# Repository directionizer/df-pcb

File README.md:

# df-pcb

Directionizer is a student project by Mason Ahner, Jared Beller, and John Fiorini for the spring 2021 session of ECE 2804 at Virginia Tech. The "directionizer" is a handheld device for locating a 1 kHz audio beacon. This repository contains KiCad schematics and PCBs for the directionizer hardware.

## Structure

The original design made during prototyping can be found in [schematic](schematic/). This was broken into three individual boards, which are stacked to form the final device. From bottom to top, the boards are [processing](processing/), [audio](audio/), and [display](display/). Each board's schematic and layout is in it's respective folder. For manufacturing, the three boards were combined into a panel. The final panel layout can be seen in the [panel](panel/) folder. Files sent to the board house, including gerbers, a bom, and smt placement, are in the [production](production/) folder.

## Licensing

Copyright (C) 2021  Mason Ahner, Jared Beller, and John Fiorini

This program is released under the [GNU General Public License, Version 3](https://www.gnu.org/licenses/gpl-3.0.txt) or later. See [LICENSE](LICENSE) for more information.

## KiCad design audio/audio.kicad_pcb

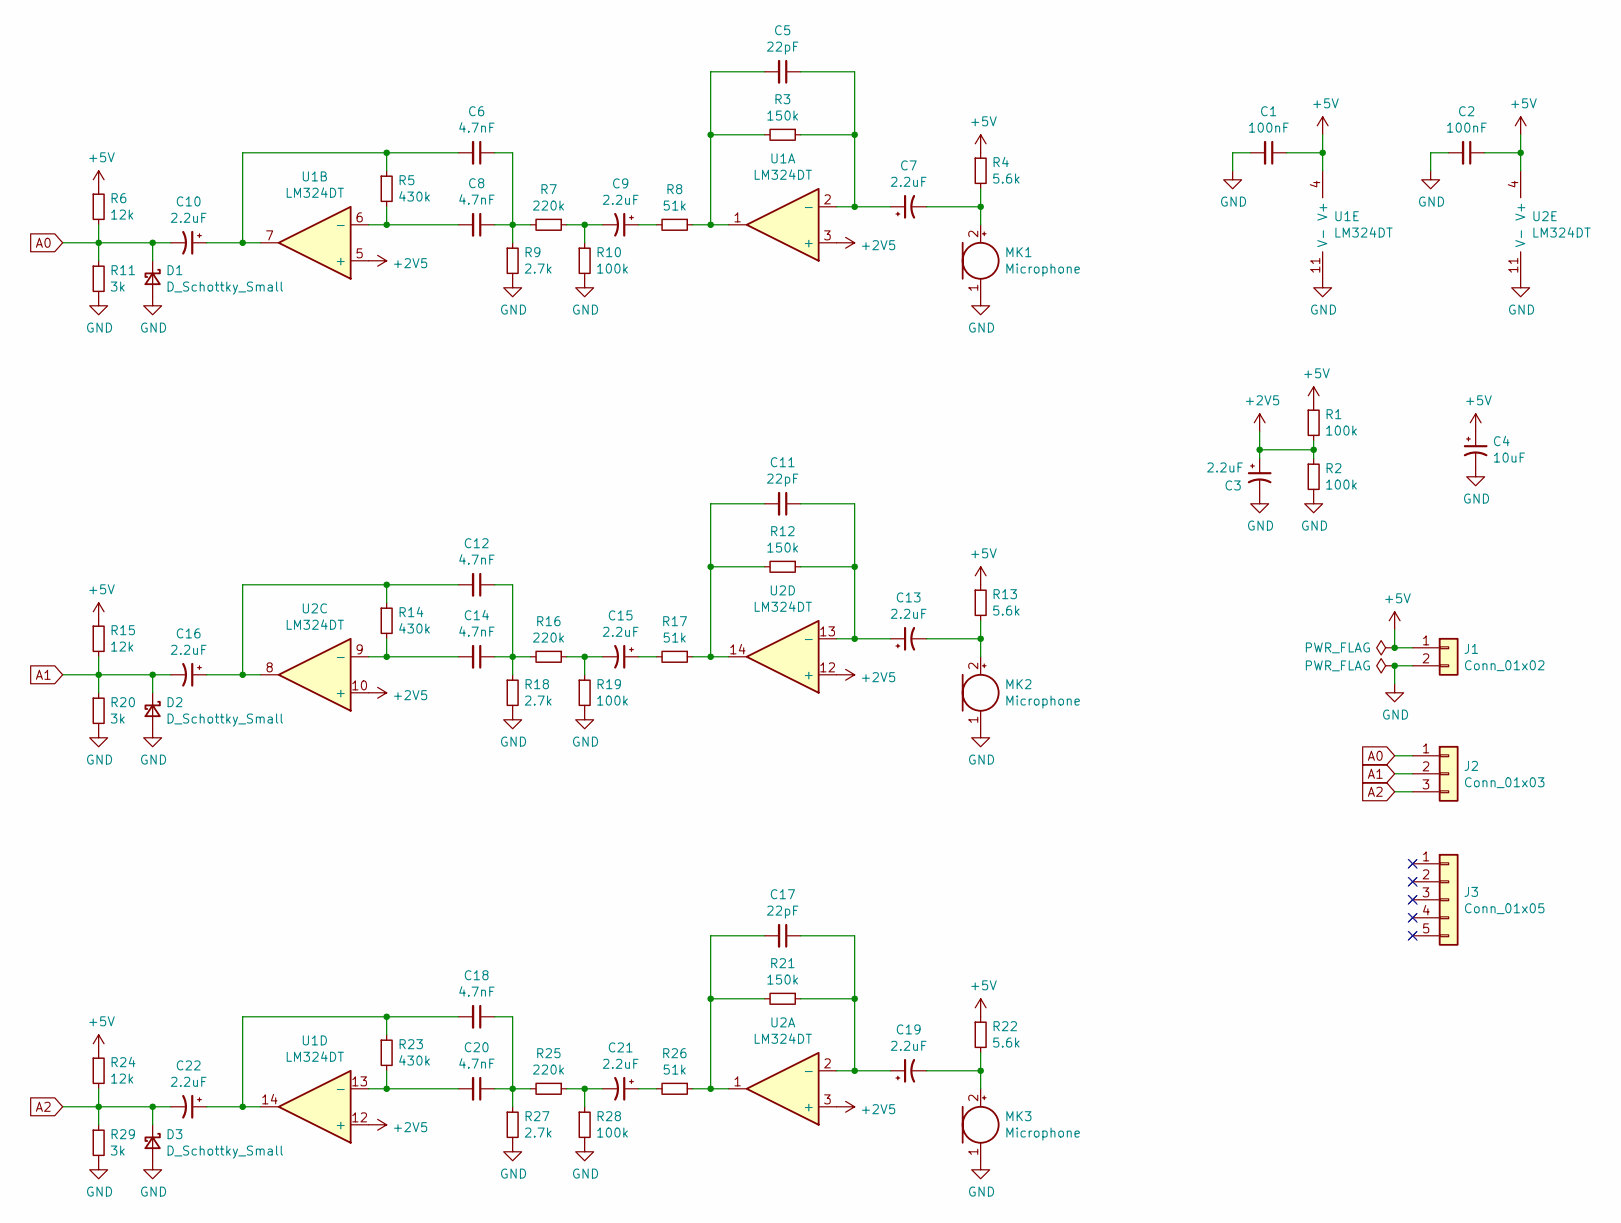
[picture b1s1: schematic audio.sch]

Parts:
C1, C2: 100nF; C_0603_1608Metric
C3, C7, C9, C10, C13, C15, C16, C19, C21, C22: 2.2uF; CP_EIA-3216-18_Kemet-A
C4: 10uF; CP_EIA-3216-18_Kemet-A
C5, C11, C17: 22pF; C_0603_1608Metric
C6, C8, C12, C14, C18, C20: 4.7nF; C_0603_1608Metric
D1, D2, D3: D_Schottky_Small; D_SOD-123
J1: Conn_01x02; 310-XX-102-41-001000
J2: Conn_01x03; 310-XX-103-41-001000
J3: Conn_01x05; 310-XX-105-41-001000
MK1, MK2, MK3: Microphone; CMA-6542PF
R1, R2, R10, R19, R28: 100k; R_0603_1608Metric
R3, R12, R21: 150k; R_0603_1608Metric
R4, R13, R22: 5.6k; R_0603_1608Metric
R5, R14, R23: 430k; R_0603_1608Metric
R6, R15, R24: 12k; R_0603_1608Metric
R7, R16, R25: 220k; R_0603_1608Metric
R8, R17, R26: 51k; R_0603_1608Metric
R9, R18, R27: 2.7k; R_0603_1608Metric
R11, R20, R29: 3k; R_0603_1608Metric
U1, U2: LM324DT; SOIC-14_3.9x8.7mm_P1.27mm

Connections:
+2V5: C3.1, R1.2, R2.1, U1.3 (+), U1.5 (+), U1.12 (+), U2.3 (+), U2.10 (+), U2.12 (+)
+5V: C1.1, C2.1, C4.1, J1.1, R1.1, R4.1, R6.1, R13.1, R15.1, R22.1, R24.1, U1.4 (V+), U2.4 (V+)
A0: C10.2, D1.1 (K), J2.1, R6.2, R11.1
A1: C16.2, D2.1 (K), J2.2, R15.2, R20.1
A2: C22.2, D3.1 (K), J2.3, R24.2, R29.1
GND: C1.2, C2.2, C3.2, C4.2, D1.2 (A), D2.2 (A), D3.2 (A), J1.2, MK1.1 (-), MK2.1 (-), MK3.1 (-), R2.2, R9.2, R10.2, R11.2, R18.2, R19.2, R20.2, R27.2, R28.2, R29.2, U1.11 (V-), U2.11 (V-)
unnamed: C5.1, C7.1, R3.1, U1.2 (-)
unnamed: C5.2, R3.2, R8.1, U1.1
unnamed: C6.1, C8.1, R7.2, R9.1
unnamed: C7.2, MK1.2 (+), R4.2
unnamed: C8.2, R5.2, U1.6 (-)
unnamed: C9.1, R8.2
unnamed: C9.2, R7.1, R10.1
unnamed: C6.2, C10.1, R5.1, U1.7
unnamed: C11.1, C13.1, R12.1, U2.13 (-)
unnamed: C11.2, R12.2, R17.1, U2.14
unnamed: C12.1, C14.1, R16.2, R18.1
unnamed: C12.2, C16.1, R14.1, U2.8
unnamed: C13.2, MK2.2 (+), R13.2
unnamed: C14.2, R14.2, U2.9 (-)
unnamed: C15.1, R17.2
unnamed: C15.2, R16.1, R19.1
unnamed: C17.1, C19.1, R21.1, U2.2 (-)
unnamed: C17.2, R21.2, R26.1, U2.1
unnamed: C18.1, C20.1, R25.2, R27.1
unnamed: C18.2, C22.1, R23.1, U1.14
unnamed: C19.2, MK3.2 (+), R22.2
unnamed: C20.2, R23.2, U1.13 (-)
unnamed: C21.1, R26.2
unnamed: C21.2, R25.1, R28.1

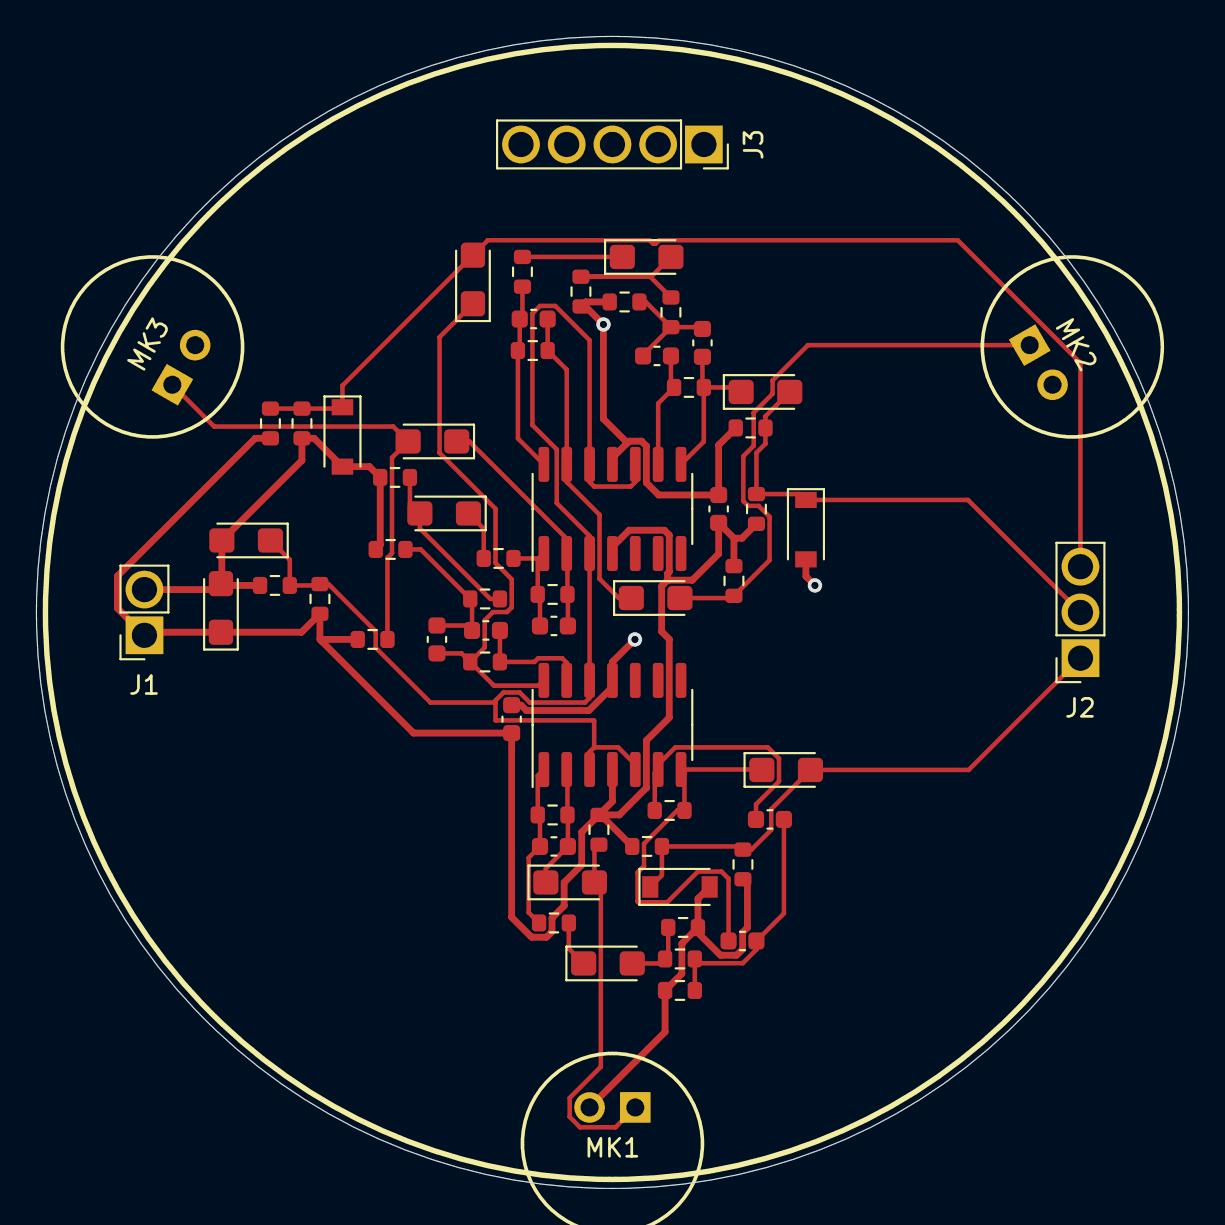
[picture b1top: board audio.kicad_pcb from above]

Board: 2 copper layers, 64.0 x 64.0 mm, 62 parts (0 on the bottom side), 30 nets.

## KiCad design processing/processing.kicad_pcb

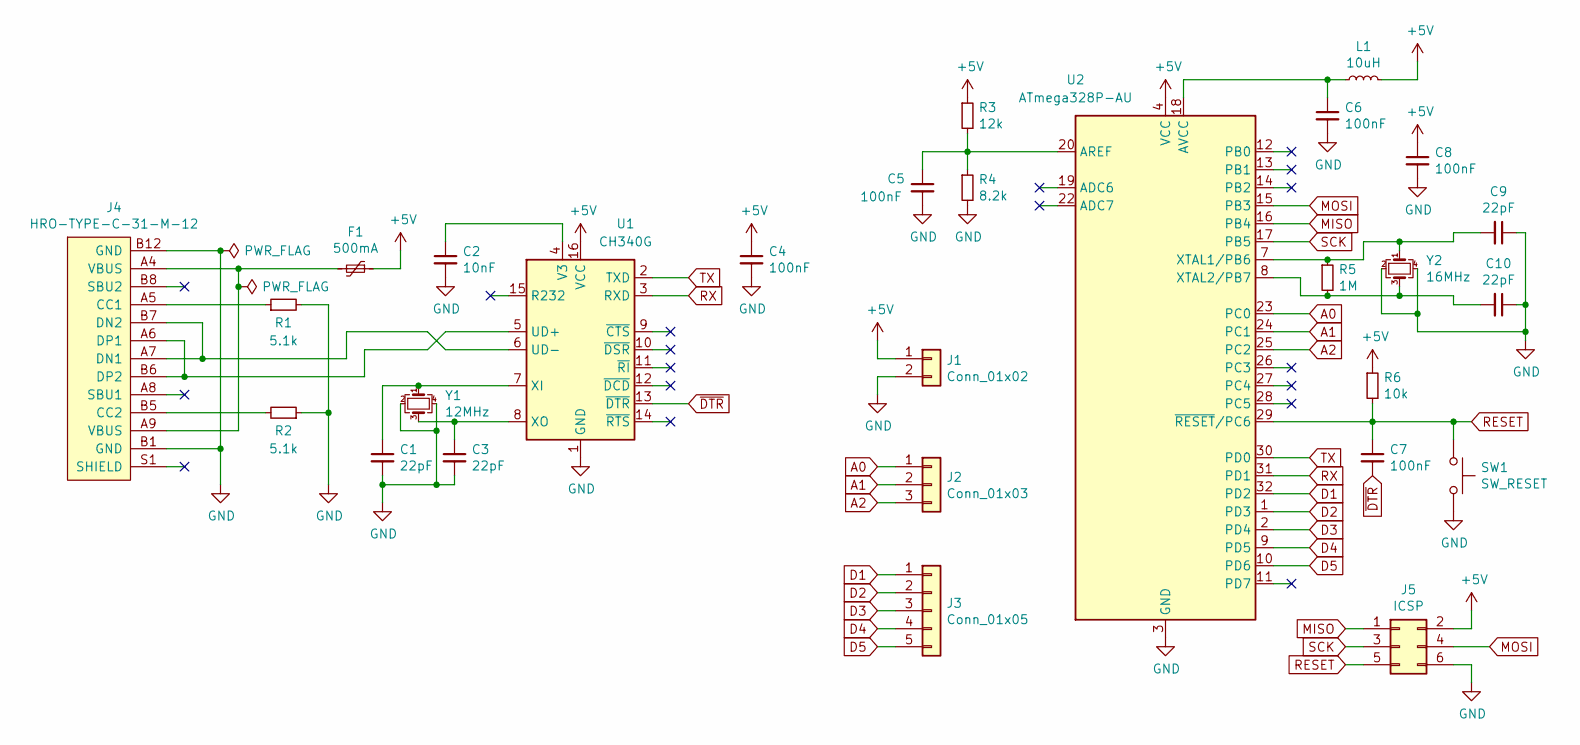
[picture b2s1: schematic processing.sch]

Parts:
C1, C3, C9, C10: 22pF; C_0603_1608Metric
C2: 10nF; C_0603_1608Metric
C4, C5, C6, C7, C8: 100nF; C_0603_1608Metric
F1: 500mA; Fuse_1206_3216Metric_Pad1.42x1.75mm_HandSolder
J1: Conn_01x02; 310-XX-102-41-001000
J2: Conn_01x03; 310-XX-103-41-001000
J3: Conn_01x05; 310-XX-105-41-001000
J4: HRO-TYPE-C-31-M-12; USB_C_Receptacle_HRO_TYPE-C-31-M-12
J5: ICSP; PinHeader_2x03_P2.54mm_Vertical
L1: 10uH; L_0805_2012Metric
R1, R2: 5.1k; R_0603_1608Metric
R3: 12k; R_0603_1608Metric
R4: 8.2k; R_0603_1608Metric
R5: 1M; R_0603_1608Metric
R6: 10k; R_1206_3216Metric
SW1: SW_RESET; SW_SPST_SKQG_WithoutStem
U1: CH340G; SOIC-16_3.9x9.9mm_P1.27mm
U2: ATmega328P-AU; TQFP-32_7x7mm_P0.8mm
Y1: 12MHz; Crystal_SMD_3225-4Pin_3.2x2.5mm
Y2: 16MHz; Crystal_SMD_3225-4Pin_3.2x2.5mm

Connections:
+5V: C4.1, C8.1, F1.1, J1.1, J5.2, L1.2, R3.1, R6.1, U1.16 (VCC), U2.4 (VCC), U2.6 (VCC)
A0: J2.1, U2.23 (PC0)
A1: J2.2, U2.24 (PC1)
A2: J2.3, U2.25 (PC2)
D1: J3.1, U2.32 (PD2)
D2: J3.2, U2.1 (PD3)
D3: J3.3, U2.2 (PD4)
D4: J3.4, U2.9 (PD5)
D5: J3.5, U2.10 (PD6)
GND: C1.2, C2.2, C3.2, C4.2, C5.2, C6.2, C8.2, C9.1, C10.1, J1.2, J4.B1 (GND), J4.B12 (GND), J5.6, R1.2, R2.1, R4.2, SW1.2, U1.1 (GND), U2.3 (GND), U2.5 (GND), U2.21 (GND), Y1.2, Y1.4, Y2.2, Y2.4
MISO: J5.1, U2.16 (PB4)
MOSI: J5.4, U2.15 (PB3)
unnamed: C1.1, U1.7 (XI), Y1.1
unnamed: C2.1, U1.4 (V3)
unnamed: C3.1, U1.8 (XO), Y1.3
unnamed: C5.1, R3.2, R4.1, U2.20 (AREF)
unnamed: C6.1, L1.1, U2.18 (AVCC)
unnamed: C9.2, R5.1, U2.7 (XTAL1/PB6), Y2.1
unnamed: C10.2, R5.2, U2.8 (XTAL2/PB7), Y2.3
unnamed: F1.2, J4.A4 (VBUS), J4.A9 (VBUS)
unnamed: J4.A5 (CC1), R1.1
unnamed: J4.A6 (DP1), J4.B6 (DP2), U1.5 (UD+)
unnamed: J4.A7 (DN1), J4.B7 (DN2), U1.6 (UD-)
unnamed: J4.B5 (CC2), R2.2
RESET: C7.1, J5.5, R6.2, SW1.1, U2.29 (~RESET~/PC6)
RX: U1.3 (RXD), U2.31 (PD1)
SCK: J5.3, U2.17 (PB5)
TX: U1.2 (TXD), U2.30 (PD0)
~DTR: C7.2, U1.13 (~DTR)

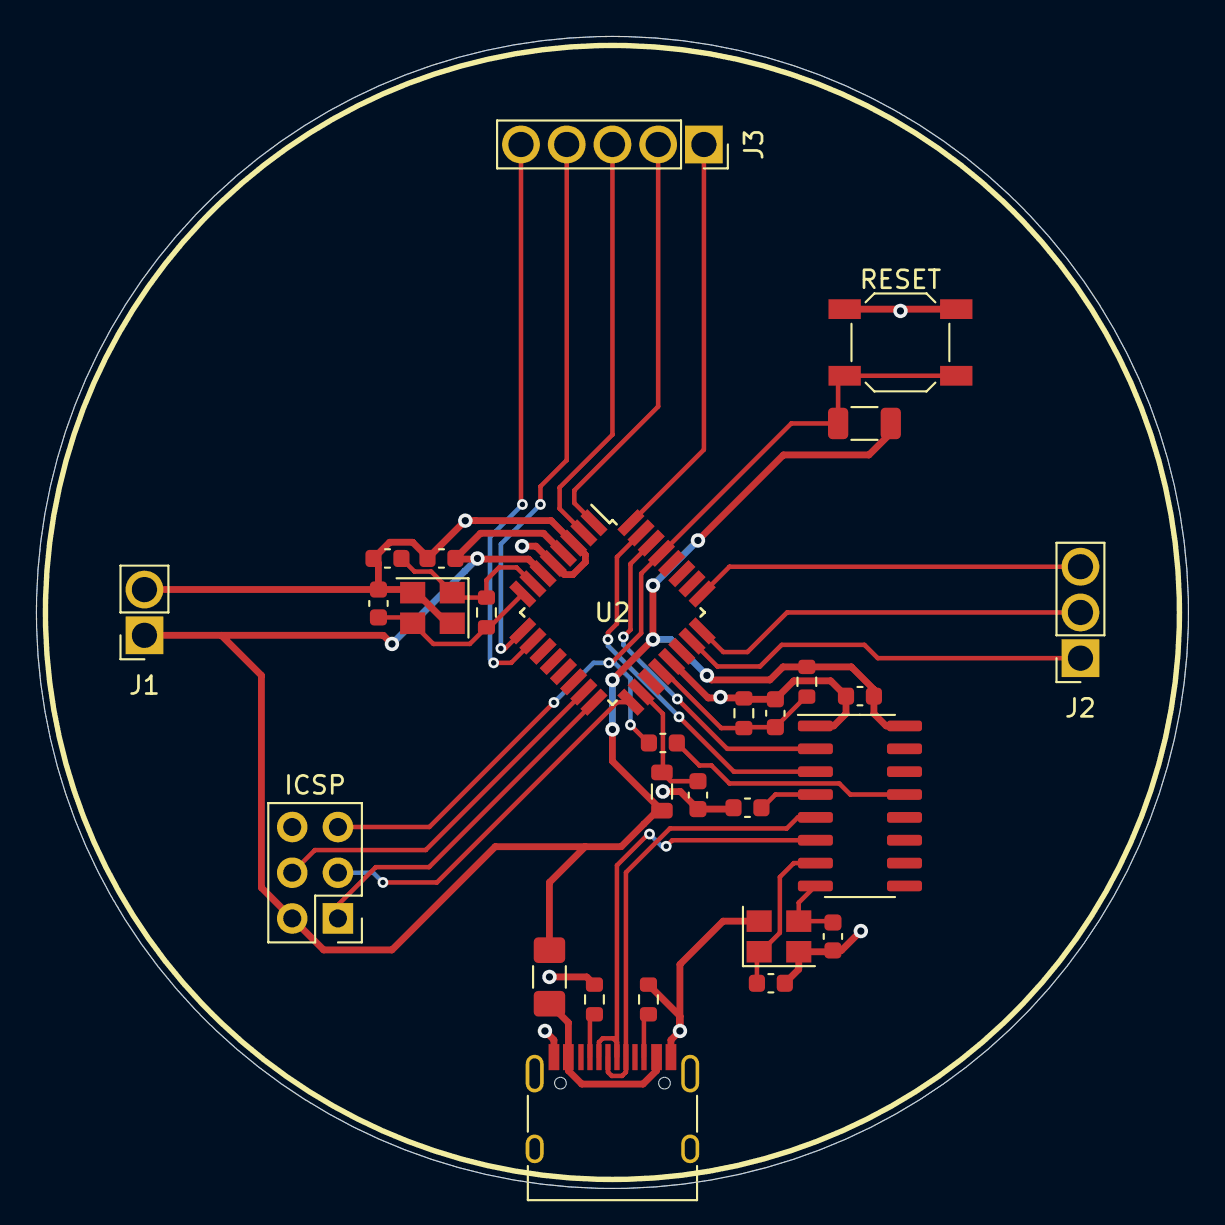
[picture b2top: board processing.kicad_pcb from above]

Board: 2 copper layers, 64.0 x 64.0 mm, 28 parts (0 on the bottom side), 29 nets.

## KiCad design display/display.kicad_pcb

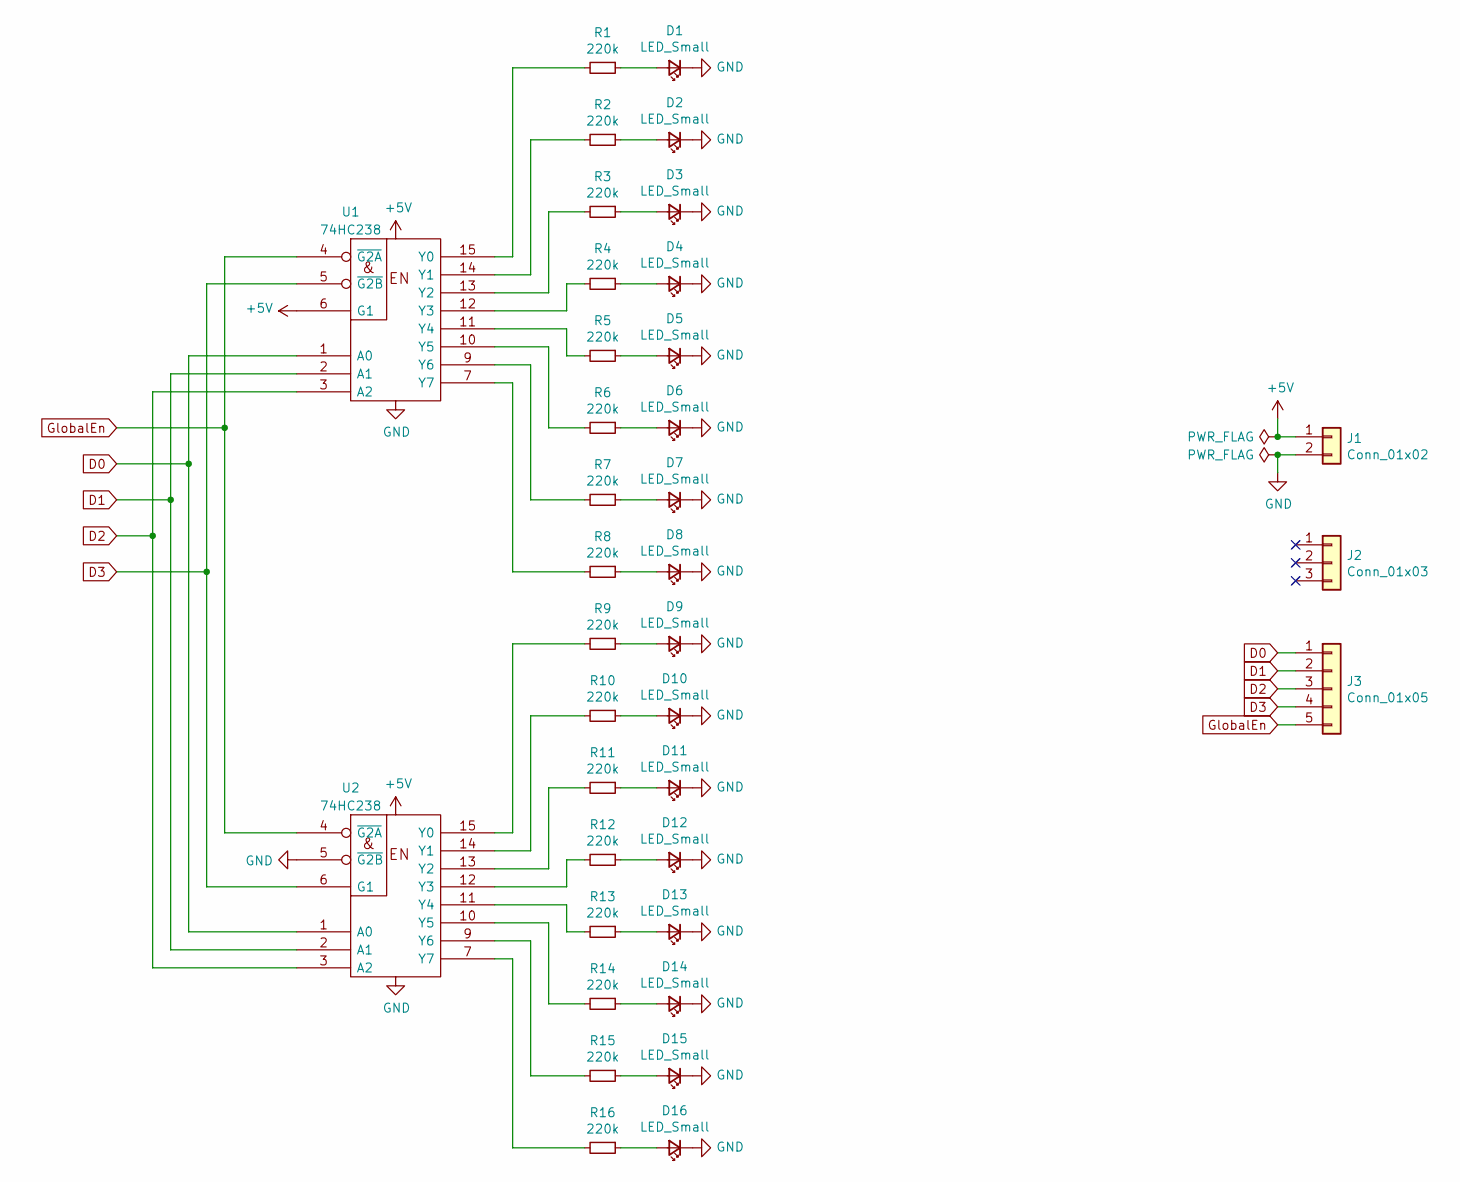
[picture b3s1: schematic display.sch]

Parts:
D1, D2, D3, D4, D5, D6, D7, D8, D9, D10, D11, D12, D13, D14, D15, D16: LED_Small; LED_D5.0mm
J1: Conn_01x02; 310-XX-102-41-001000
J2: Conn_01x03; 310-XX-103-41-001000
J3: Conn_01x05; 310-XX-105-41-001000
R1, R2, R3, R4, R5, R6, R7, R8, R9, R10, R11, R12, R13, R14, R15, R16: 220k; R_0603_1608Metric
U1, U2: 74HC238; SOIC-16_3.9x9.9mm_P1.27mm

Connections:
+5V: J1.1, U1.6 (G1), U1.16 (VCC), U2.16 (VCC)
D0: J3.1, U1.1 (A0), U2.1 (A0)
D1: J3.2, U1.2 (A1), U2.2 (A1)
D2: J3.3, U1.3 (A2), U2.3 (A2)
D3: J3.4, U1.5 (~G2B), U2.6 (G1)
GND: D1.1 (K), D2.1 (K), D3.1 (K), D4.1 (K), D5.1 (K), D6.1 (K), D7.1 (K), D8.1 (K), D9.1 (K), D10.1 (K), D11.1 (K), D12.1 (K), D13.1 (K), D14.1 (K), D15.1 (K), D16.1 (K), J1.2, U1.8 (GND), U2.5 (~G2B), U2.8 (GND)
GlobalEn: J3.5, U1.4 (~G2A), U2.4 (~G2A)
unnamed: D1.2 (A), R1.1
unnamed: D2.2 (A), R2.1
unnamed: D3.2 (A), R3.1
unnamed: D4.2 (A), R4.1
unnamed: D5.2 (A), R5.1
unnamed: D6.2 (A), R6.1
unnamed: D7.2 (A), R7.1
unnamed: D8.2 (A), R8.1
unnamed: D9.2 (A), R9.1
unnamed: D10.2 (A), R10.1
unnamed: D11.2 (A), R11.1
unnamed: D12.2 (A), R12.1
unnamed: D13.2 (A), R13.1
unnamed: D14.2 (A), R14.1
unnamed: D15.2 (A), R15.1
unnamed: D16.2 (A), R16.1
unnamed: R1.2, U1.15 (Y0)
unnamed: R2.2, U1.14 (Y1)
unnamed: R3.2, U1.13 (Y2)
unnamed: R4.2, U1.12 (Y3)
unnamed: R5.2, U1.11 (Y4)
unnamed: R6.2, U1.10 (Y5)
unnamed: R7.2, U1.9 (Y6)
unnamed: R8.2, U1.7 (Y7)
unnamed: R9.2, U2.15 (Y0)
unnamed: R10.2, U2.14 (Y1)
unnamed: R11.2, U2.13 (Y2)
unnamed: R12.2, U2.12 (Y3)
unnamed: R13.2, U2.11 (Y4)
unnamed: R14.2, U2.10 (Y5)
unnamed: R15.2, U2.9 (Y6)
unnamed: R16.2, U2.7 (Y7)

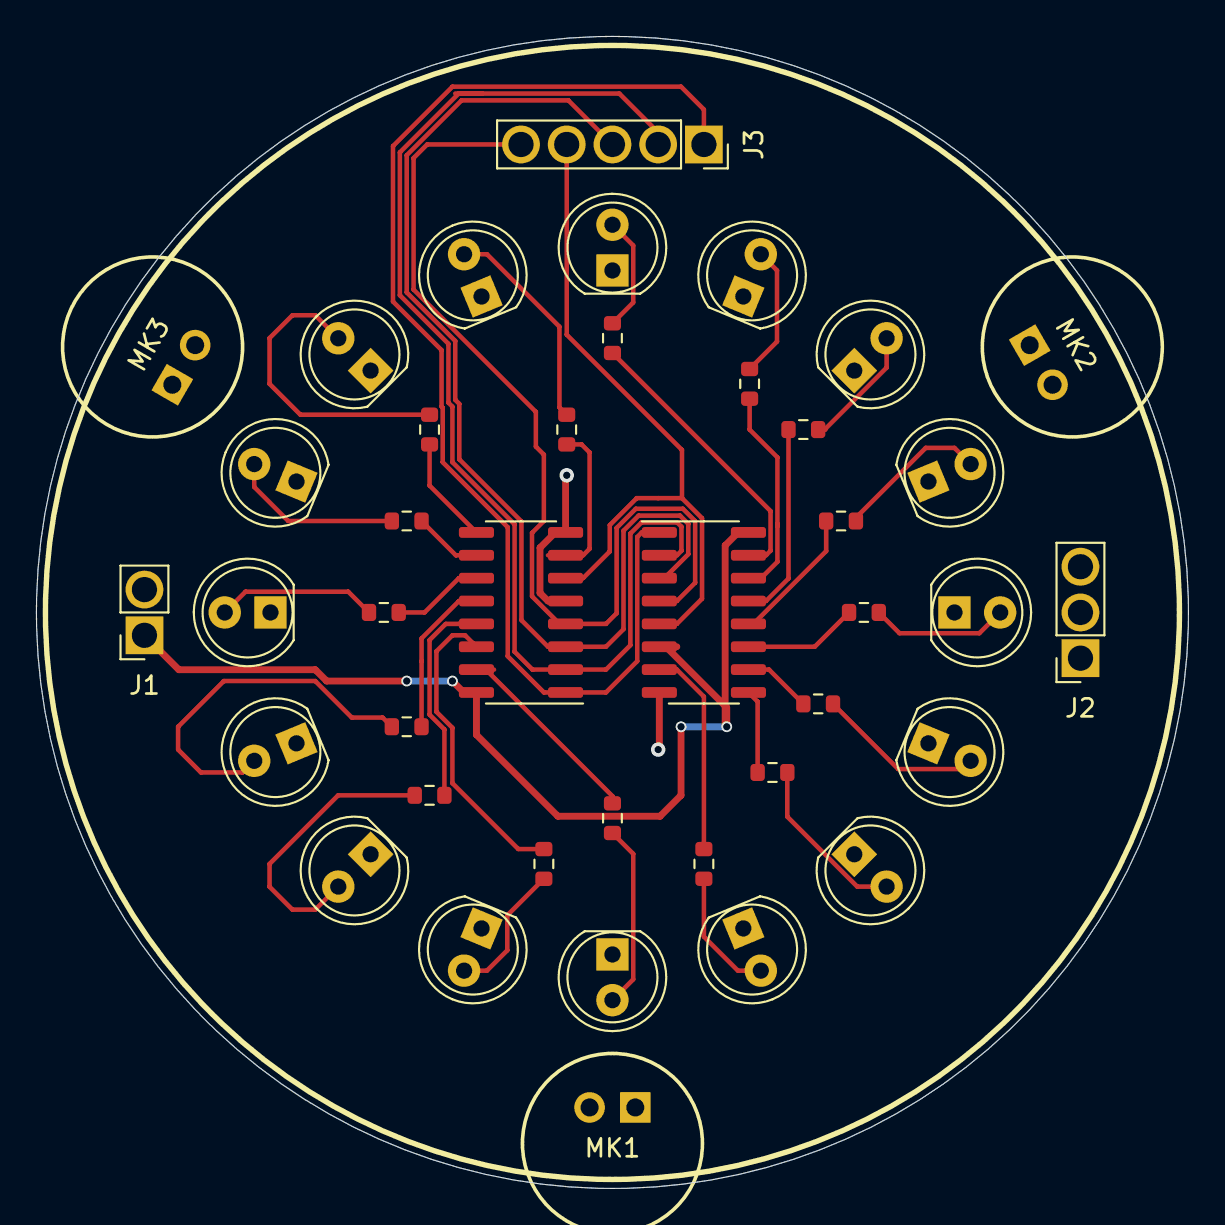
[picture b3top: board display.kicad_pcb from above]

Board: 2 copper layers, 64.0 x 64.0 mm, 40 parts (0 on the bottom side), 39 nets.

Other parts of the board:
MK1, MK2, MK3: Microphone; CMA-6542PF

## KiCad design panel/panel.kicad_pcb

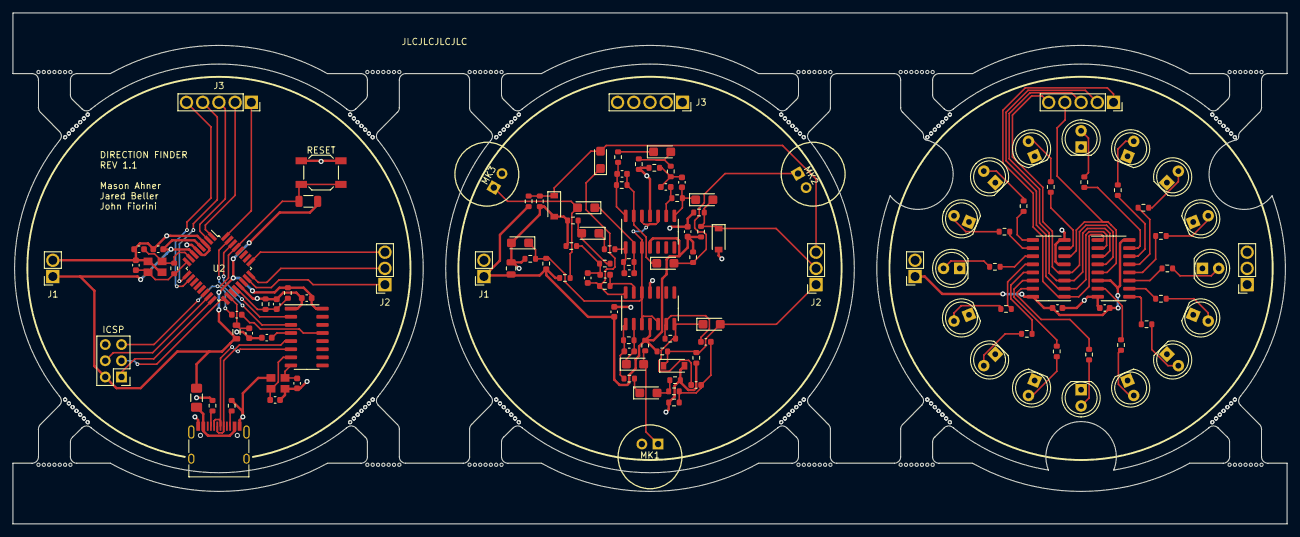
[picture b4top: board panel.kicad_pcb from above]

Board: 2 copper layers, 199.5 x 80.0 mm, 129 parts (0 on the bottom side), 85 nets.

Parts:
C1, C3, C9, C10, C15, C21, C27: 22pF; C_0603_1608Metric
C2: 10nF; C_0603_1608Metric
C4, C5, C6, C7, C8, C11, C12, C33, C34: 100nF; C_0603_1608Metric
C13, C17, C19, C20, C23, C25, C26, C29, C31, C32: 2.2uF; CP_EIA-3216-18_Kemet-A
C14: 10uF; C_0805_2012Metric
C16, C18, C22, C24, C28, C30: 4.7nF; C_0603_1608Metric
D1, D2, D3: D_Schottky_Small; D_SOD-123
D1#2, D2#2, D3#2, D4, D5, D6, D7, D8, D9, D10, D11, D12, D13, D14, D15, D16: LED_Small; LED_D5.0mm
F1: 500mA; Fuse_1206_3216Metric_Pad1.42x1.75mm_HandSolder
J1, J1#2, J1#3: Conn_01x02; 310-XX-102-41-001000
J2, J2#2, J2#3: Conn_01x03; 310-XX-103-41-001000
J3, J3#2, J3#3: Conn_01x05; 310-XX-105-41-001000
J4: HRO-TYPE-C-31-M-12; USB_C_Receptacle_HRO_TYPE-C-31-M-12
J5: ICSP; PinHeader_2x03_P2.54mm_Vertical
L1: 10uH; L_0805_2012Metric
MK1, MK2, MK3: Microphone; CMA-6542PF
R1, R2: 5.1k; R_0603_1608Metric
R3, R12, R21, R30: 12k; R_0603_1608Metric
R4: 8.2k; R_0603_1608Metric
R5, R9, R18, R27: 1M; R_0603_1608Metric
R6: 10k; R_1206_3216Metric
R7, R8, R16, R25, R34: 100k; R_0603_1608Metric
R10, R19, R28: 5.6k; R_0603_1608Metric
R11, R20, R29: 430k; R_0603_1608Metric
R13, R22, R31: 220k; R_0603_1608Metric
R14, R23, R32: 51k; R_0603_1608Metric
R15, R24, R33: 2.7k; R_0603_1608Metric
R17, R26, R35: 3k; R_0603_1608Metric
R36: 680; R_0603_1608Metric
R37, R38, R39, R41, R42, R43, R45, R46, R47, R49, R50, R51: 390; R_0603_1608Metric
R40, R44, R48: 330; R_0603_1608Metric
SW1: SW_RESET; SW_SPST_SKQG_WithoutStem
U1: CH340G; SOIC-16_3.9x9.9mm_P1.27mm
U2: ATmega328P-AU; TQFP-32_7x7mm_P0.8mm
U3, U4: LM324DT; SOIC-14_3.9x8.7mm_P1.27mm
U5, U6: 74HC238; SOIC-16_3.9x9.9mm_P1.27mm
Y1: 12MHz; Crystal_SMD_3225-4Pin_3.2x2.5mm
Y2: 16MHz; Crystal_SMD_3225-4Pin_3.2x2.5mm

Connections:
+2V5: C13.1, R7.2, R8.1, U3.3, U3.5, U3.12, U4.3, U4.10, U4.12
+5V: C4.1, C8.1, C11.1, C12.1, C14.1, C33.1, C34.1, F1.1, J1.1, J1#2.1, J1#3.1, J5.2, L1.2, R3.1, R6.1, R7.1, R10.1, R12.1, R19.1, R21.1, R28.1, R30.1, U1.16, U2.4, U2.6, U3.4, U4.4, U5.6, U5.16, U6.16
A0: C20.2, D1.1, J2#2.1, J2#3.1, R12.2, R17.1, U2.23
A1: C26.2, D2.1, J2#2.2, J2#3.2, R21.2, R26.1, U2.24
A2: C32.2, D3.1, J2#2.3, J2#3.3, R30.2, R35.1, U2.25
D0: J3.1, U5.1, U6.1
D1: J3.2, J3#3.1, U2.32, U5.2, U6.2
D2: J3.3, J3#3.2, U2.1, U5.3, U6.3
D3: J3.4, J3#3.3, U2.2, U5.5, U6.6
D4: J3#3.4, U2.9
D5: J3#3.5, U2.10
GND: C1.2, C2.2, C3.2, C4.2, C5.2, C6.2, C8.2, C9.1, C10.1, C11.2, C12.2, C13.2, C14.2, C33.2, C34.2, D1.2, D1#2.1, D2.2, D2#2.1, D3.2, D3#2.1, D4.1, D5.1, D6.1, D7.1, D8.1, D9.1, D10.1, D11.1, D12.1, D13.1, D14.1, D15.1, D16.1, J1.2, J1#2.2, J1#3.2, J4.B1, J4.B12, J5.6, MK1.1, MK2.1, MK3.1, R1.2, R2.1, R4.2, R8.2, R15.2, R16.2, R17.2, R24.2, R25.2, R26.2, R33.2, R34.2, R35.2, SW1.2, U1.1, U2.3, U2.5, U2.21, U3.11, U4.11, U5.8, U6.5, U6.8, Y1.2, Y1.4, Y2.2, Y2.4
GlobalEn: J3.5, U5.4, U6.4
MISO: J5.1, U2.16
MOSI: J5.4, U2.15
unnamed: C1.1, U1.7, Y1.1
unnamed: C2.1, U1.4
unnamed: C3.1, U1.8, Y1.3
unnamed: C5.1, C15.1, C17.1, R3.2, R4.1, R9.1, U2.20, U3.2
unnamed: C15.2, R9.2, R14.1, U3.1
unnamed: C6.1, C16.1, C18.1, L1.1, R13.2, R15.1, U2.18
unnamed: C17.2, MK1.2, R10.2
unnamed: C18.2, R11.2, U3.6
unnamed: C19.1, R14.2
unnamed: C9.2, C19.2, R5.1, R13.1, R16.1, U2.7, Y2.1
unnamed: C16.2, C20.1, R11.1, U3.7
unnamed: C10.2, R5.2, U2.8, Y2.3
unnamed: C21.1, C23.1, R18.1, U4.13
unnamed: C21.2, R18.2, R23.1, U4.14
unnamed: C22.1, C24.1, R22.2, R24.1
unnamed: C22.2, C26.1, R20.1, U4.8
unnamed: C23.2, MK2.2, R19.2
unnamed: C24.2, R20.2, U4.9
unnamed: C25.1, R23.2
unnamed: C25.2, R22.1, R25.1
unnamed: C27.1, C29.1, R27.1, U4.2
unnamed: C27.2, R27.2, R32.1, U4.1
unnamed: C28.1, C30.1, R31.2, R33.1
unnamed: C28.2, C32.1, R29.1, U3.14
unnamed: C29.2, MK3.2, R28.2
unnamed: C30.2, R29.2, U3.13
unnamed: C31.1, R32.2
unnamed: C31.2, R31.1, R34.1
unnamed: D1#2.2, R36.1
unnamed: D2#2.2, R37.1
unnamed: D3#2.2, R38.1
unnamed: D4.2, R39.1
unnamed: D5.2, R40.1
unnamed: D6.2, R41.1
unnamed: D7.2, R42.1
unnamed: D8.2, R43.1
unnamed: D9.2, R44.1
unnamed: D10.2, R45.1
unnamed: D11.2, R46.1
unnamed: D12.2, R47.1
unnamed: D13.2, R48.1
unnamed: D14.2, R49.1
unnamed: D15.2, R50.1
unnamed: D16.2, R51.1
unnamed: F1.2, J4.A4, J4.A9
unnamed: J4.A5, R1.1
unnamed: J4.A6, J4.B6, U1.5
unnamed: J4.A7, J4.B7, U1.6
unnamed: J4.B5, R2.2
unnamed: R36.2, U5.15
unnamed: R37.2, U5.14
unnamed: R38.2, U5.13
unnamed: R39.2, U5.12
unnamed: R40.2, U5.11
unnamed: R41.2, U5.10
unnamed: R42.2, U5.9
unnamed: R43.2, U5.7
unnamed: R44.2, U6.15
unnamed: R45.2, U6.14
unnamed: R46.2, U6.13
unnamed: R47.2, U6.12
unnamed: R48.2, U6.11
unnamed: R49.2, U6.10
unnamed: R50.2, U6.9
unnamed: R51.2, U6.7
RESET: C7.1, J5.5, R6.2, SW1.1, U2.29
RX: U1.3, U2.31
SCK: J5.3, U2.17
TX: U1.2, U2.30
~DTR: C7.2, U1.13

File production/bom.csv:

Comment,Designator,Footprint,LCSC Part No.
22pF,"C1,C3,C9,C10,C15,C21,C27",0603,C1653
4.7nF,"C16,C18,C22,C24,C28,C30",0603,C53987
10nF,C2,0603,C57112
100nF,"C4,C5,C6,C7,C8,C11,C12,C33,C34",0603,C14663
2.2uF,"C13,C17,C19,C20,C23,C25,C26,C29,C31,C32",3216,C179115
10uF,C14,0805,C15850
10uH,L1,0805,C1046
330R,"R40,R44,R48",0603,C23138
390R,"R37,R38,R39,R41,R42,R43,R45,R46,R47,R49,R50,R51",0603,C23151
680R,R36,0603,C23228
2.7k,"R15,R24,R33",0603,C13167
3k,"R17,R26,R35",0603,C4211
5.1k,"R1,R2",0603,C23186
5.6k,"R10,R19,R28",0603,C23189
8.2k,R4,0603,C25981
10k,R6,1206,C17902
12k,"R3,R12,R21,R30",0603,C22790
51k,"R14,R23,R32",0603,C23196
100k,"R7,R8,R16,R25,R34",0603,C25803
220k,"R13,R22,R31",0603,C22961
430k,"R11,R20,R29",0603,C25969
1M,"R5,R9,R18,R27",0603,C22935
12MHz,Y1,3225,C9002
16MHz,Y2,3225,C13738
Schottky,"D1,D2,D3",SOD-123,C8598
Push Button,SW1,SPST_SKQG,C318884
CH340G,U1,SOIC-16,C14267
ATmega328P-AU,U2,TQFP-32,C14877
LM324DT,"U3,U4",SOIC-14,C71035
74HC238,"U5,U6",SOIC-16,C5620
TYPE-C-31-M-12,"J4","TYPE-C-31_L8.94_W7.3",C165948

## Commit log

2021-02-23 initial schematic stuff
2021-03-09 update main schematic
2021-03-10 initial processing board
2021-03-13 audio system approved
2021-03-14 base audio board
2021-03-14 properly orient pcb
2021-03-15 finish the processing board
2021-03-16 kind of messed with the "rats nest"
2021-03-16 routing wires
2021-03-16 added display pcb schematic
2021-03-17 2nd mic added
2021-03-18 fix design rules
2021-03-18 display board template
2021-03-18 resize boards
2021-03-19 Finished adding audio pcb tracks
2021-03-20 display pcb wired
2021-03-22 panelized and ready for manufacturing
2021-04-04 errata 1: rx and tx are flipped
2021-05-24 errata 2: fix footprints
2021-05-29 prepare for release
